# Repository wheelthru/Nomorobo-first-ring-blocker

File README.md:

# First-ring blocker for Nomorobo

This tool blocks the first ring of all incoming calls, avoiding the annoying one-ring-and-silence from calls the great Nomorobo service blocks. This is at the cost of real callers having to wait one extra ring before we pick up.  Oh Well.

## Description

The real documentation of this project is here: [http://jimlaurwilliams.org/wordpress/?p=6738](http://jimlaurwilliams.org/wordpress/?p=6738) 

Its ATtiny85 basically controls a normally closed relay in series with the incoming phone line (here a VOIP ATA), opening the contacts a few milliseconds into the first ring, before phones can ring.  It reconnects quickly after the first ring, in hopes of not screwing with the Caller ID sent between rings.

This was built and tuned for my situation, with parts from my junkbox, and probably isn't a drop-in for anybody else.  OK, maybe if they have a Arris TG1682G modem providing their VOIP phone connections.  It was posted here at the request of someone who saw the post in my Project Notes.

The Eagle (7.7.0) files for the PCB I made up for mine are included here.  Unless your junkbox contains the same parts as mine, the board layout probably isn't useful.

Code for the ATtiny85 on the PCB, developed with Arduino IDE 1.8.x, is  in **Nomorobo85Msg.ino**.  A Nano displays stats (rings, blocks) on a 1620 LCD.  Serial communication from the main PCB (via SoftwareSerial) tells the Nano what to show.  The Nano's code is **LcdHostNanoMsg1.ino**.  There are various comments and historical leftovers in both those files.

## Author

Jim Williams (a member of [Workshop88](http://workshop88.com))

## Acknowledgments

Inspired as an improvement on the very useful [Nomorobo](https://www.nomorobo.com/) service.

Special thanks to Aaron Foss for the cool Nomorobo T shirt!

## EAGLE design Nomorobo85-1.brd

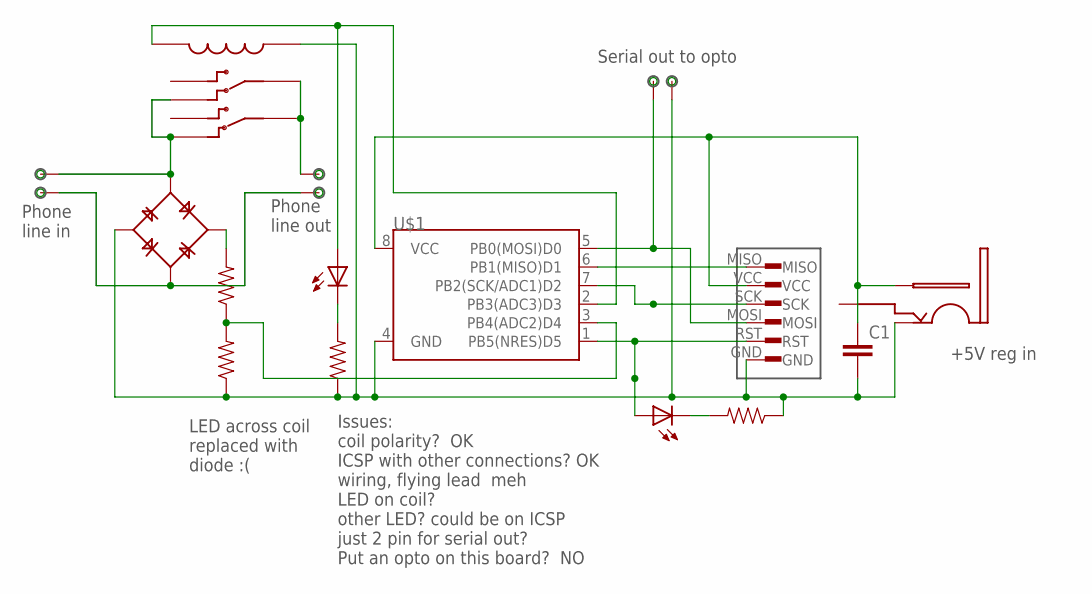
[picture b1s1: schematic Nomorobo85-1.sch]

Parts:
C1: CAP1206; 1206
U$1: ATTINY85SO08-I-HAVE-THESE; SO08-EIAJ
U$2, U$3, U$4, U$9: RESISTOR1206WW; 1206WW
U$5: BRIDGE-ROUNDMY-600V-1A; BRIDGE-ROUND
U$6: M2X3-HEADERICSP-LONGPADS; M2X3-LONGPADS
U$7, U$8: SOLDER-PAD-2LONGPADS; 02P
U$10: BARREL-COAX-PWR; BARREL-COAX-CONNECTOR
U$11, U$14: LED-12061206; 1206W
U$12: RELAY-DPDT
U$13: SOLDER-PAD-2LONGPPAD2; SOLDER-PAD-2-LONGPADS

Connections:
GND: C1.2, U$1.4 (GND), U$2.1, U$4.1, U$5.OUT- (V-), U$6.GND, U$9.1, U$10.SHELL, U$12.COIL+, U$13.P$2
unnamed: U$1.1 (PB5(NRES)D5), U$6.RST, U$14.1 (A)
unnamed: U$5.AC1 (IN1), U$7.1, U$12.NC1, U$12.NC2
unnamed: U$1.5 (PB0(MOSI)D0), U$6.MOSI, U$13.P$3
unnamed: U$1.2 (PB3(ADC3)D3), U$11.1 (A), U$12.COIL-
unnamed: U$1.6 (PB1(MISO)D1), U$6.MISO
unnamed: U$8.2, U$12.COM1, U$12.COM2
unnamed: U$1.3 (PB4(ADC2)D4), U$3.1, U$4.2
unnamed: U$3.2, U$5.OUT+ (V+)
unnamed: U$9.2, U$11.2 (C)
unnamed: U$5.AC2 (IN2), U$7.2, U$8.1
unnamed: U$2.2, U$14.2 (C)
unnamed: U$1.7 (PB2(SCK/ADC1)D2), U$6.SCK
VCC: C1.1, U$1.8 (VCC), U$6.VCC, U$10.PIN

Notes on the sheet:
Serial out to opto
+5V reg in
Phone line in
Phone line out
Issues: coil polarity? OK ICSP with other connections? OK wiring, flying lead meh LED on coil? other LED? could be on ICSP just 2 pin for serial out? Put an opto on this board? NO
LED across coil replaced with diode :(

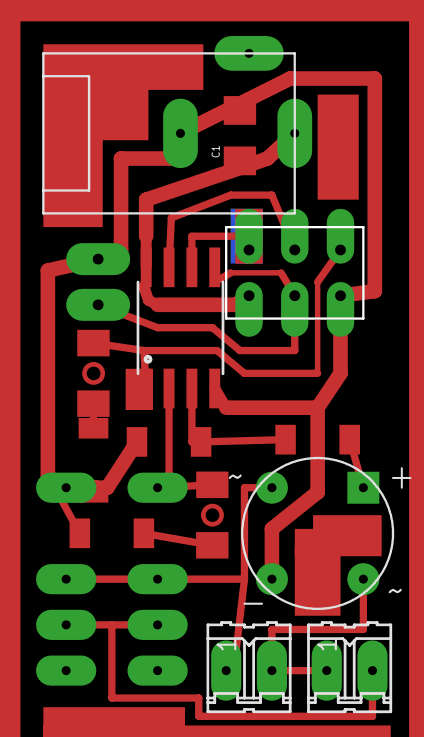
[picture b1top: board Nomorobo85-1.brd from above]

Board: 2 copper layers, 15 parts (1 on the bottom side), 14 nets.

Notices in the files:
parts and their libraries:
jim: Licensing: CC v3.0 Share-Alike You are welcome to use this library for commercial purposes.
